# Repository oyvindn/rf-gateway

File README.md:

# rf-gateway

## Hardware

* [ESP32-WROOM-32D](https://www.espressif.com/sites/default/files/documentation/esp32-wroom-32d_esp32-wroom-32u_datasheet_en.pdf)
* [HopeRF RFM69CW 13DBM 868Mhz RF Transceiver Module](https://www.hoperf.com/modules/rf_transceiver/RFM69C.html)
* DS18B20 Digital temperature sensor

## Arduino sketch dependencies

* [Arduino core for the ESP32](https://github.com/espressif/arduino-esp32)
* [Arduino Client for MQTT](https://pubsubclient.knolleary.net/index.html)
* [RadioHead Packet Radio library for embedded microprocessors](http://www.airspayce.com/mikem/arduino/RadioHead/)

## Compile, upload and monitor ESP32 using the Arduino CLI

### Add secrets
Copy `arduino_secrets.h.example` to `arduino_secrets.h` and change the example secret values.

### Download and install Arduino IDE and/or CLI
[Arduino CLI](https://arduino.github.io/arduino-cli/) is an all-in-one solution that provides Boards/Library Managers, sketch builder, board detection, uploader, and many other tools needed to use any Arduino compatible board and platform from command line or machine interfaces.

### Initialiazies a Arduino CLI new configuration:
`arduino-cli config init`

### Add URL for Arduino core for the ESP32, ESP32-S2 and ESP32-C3
Edit `~/Library/Arduino15/arduino-cli.yaml` and add:

```
board_manager:
  additional_urls:
  - https://raw.githubusercontent.com/espressif/arduino-esp32/gh-pages/package_esp32_index.json
```

### Update the core list
`arduino-cli core update-index`

### Install Arduino core for the ESP32, ESP32-S2 and ESP32-C3
`arduino-cli core install esp32:esp32`

### Compile sketch
`arduino-cli compile -b esp32:esp32:esp32 rf-gateway.ino`

### Upload sketch to ESP32:
`arduino-cli upload -p /dev/cu.usbserial-A600K4HV -b esp32:esp32:esp32 rf-gateway.ino`

### Open the serial monitor
`arduino-cli monitor -p /dev/cu.usbserial-A600K4HV -c baudrate=115200`

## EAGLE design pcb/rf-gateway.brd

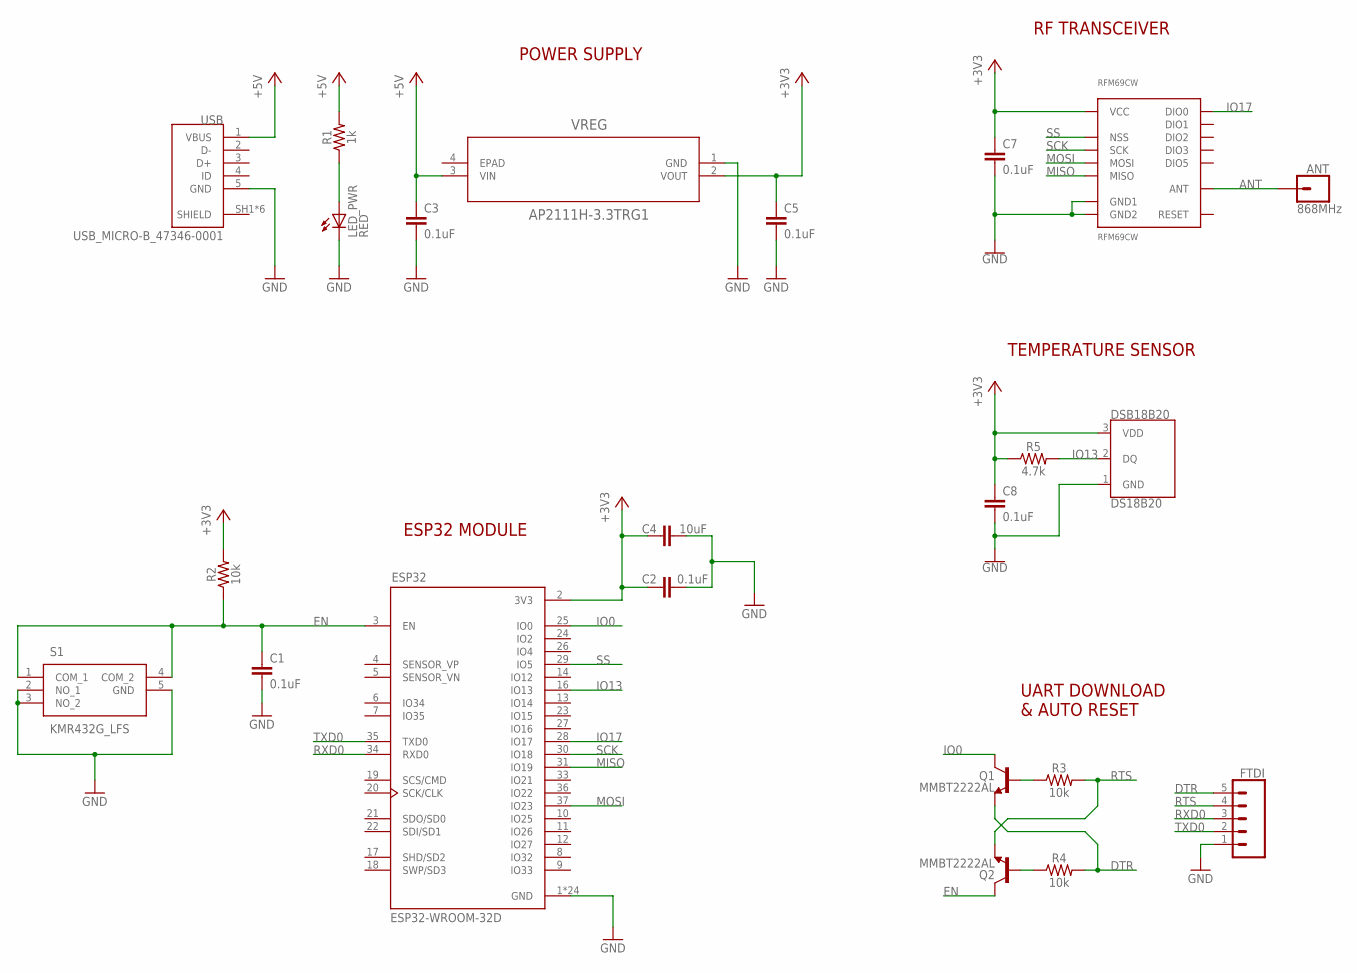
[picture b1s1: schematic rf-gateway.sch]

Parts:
ANT: 868MHz; 1X01
C1, C2, C3, C5, C7, C8: 0.1uF; 0603
C4: 10uF; 0805
DSB18B20: DS18B20; TO-92-AMMO
ESP32: ESP32-WROOM-32D
FTDI: CONN_05; 1X05
LED_PWR: RED; CHIPLED_0805
Q1, Q2: MMBT2222AL; SOT23-3
R1: 1k; 0603
R2, R3, R4: 10k; 0603
R5: 4.7k; 0603
RFM69CW: RFM69CW
S1: KMR432G_LFS; KMR421GULCLFS
USB: USB_MICRO-B_47346-0001; MOLEX_47346-0001
VREG: AP2111H-3.3TRG1; SOT-223_DIO

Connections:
+3V3: C2.1, C4.1, C5.1, C7.1, C8.1, DSB18B20.3 (VDD), ESP32.2 (3V3), R2.2, R5.1, RFM69CW.VDD (VCC), VREG.2 (VOUT)
+5V: C3.1, R1.2, USB.1 (VBUS), VREG.3 (VIN)
ANT: ANT.1, RFM69CW.ANT
DTR: FTDI.5, Q1.2 (E), R4.2
EN: C1.1, ESP32.3 (EN), Q2.3 (C), R2.1, S1.1 (COM_1), S1.4 (COM_2)
GND: C1.2, C2.2, C3.2, C4.2, C5.2, C7.2, C8.2, DSB18B20.1 (GND), ESP32.1 (GND), ESP32.15 (GND), ESP32.38 (GND), ESP32.39_1 (GND), ESP32.39_2 (GND), ESP32.39_3 (GND), ESP32.39_4 (GND), ESP32.39_5 (GND), ESP32.39_6 (GND), ESP32.39_7 (GND), ESP32.39_8 (GND), ESP32.39_9 (GND), ESP32.39_10 (GND), ESP32.39_11 (GND), ESP32.39_12 (GND), ESP32.39_13 (GND), ESP32.39_14 (GND), ESP32.39_15 (GND), ESP32.39_16 (GND), ESP32.39_17 (GND), ESP32.39_18 (GND), ESP32.39_19 (GND), ESP32.39_20 (GND), ESP32.39_21 (GND), FTDI.1, LED_PWR.C, RFM69CW.GND@1 (GND1), RFM69CW.GND@2 (GND2), S1.2 (NO_1), S1.3 (NO_2), S1.5 (GND), USB.5 (GND), VREG.1 (GND)
IO0: ESP32.25 (IO0), Q1.3 (C)
IO13: DSB18B20.2 (DQ), ESP32.16 (IO13), R5.2
IO17: ESP32.28 (IO17), RFM69CW.DIO0
MISO: ESP32.31 (IO19), RFM69CW.MISO
MOSI: ESP32.37 (IO23), RFM69CW.MOSI
unnamed: LED_PWR.A, R1.1
unnamed: Q1.1 (B), R3.1
unnamed: Q2.1 (B), R4.1
RTS: FTDI.4, Q2.2 (E), R3.2
RXD0: ESP32.34 (RXD0), FTDI.3
SCK: ESP32.30 (IO18), RFM69CW.SCK
SS: ESP32.29 (IO5), RFM69CW.NSS
TXD0: ESP32.35 (TXD0), FTDI.2

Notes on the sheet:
ESP32 MODULE
UART DOWNLOAD & AUTO RESET
POWER SUPPLY
RF TRANSCEIVER
TEMPERATURE SENSOR

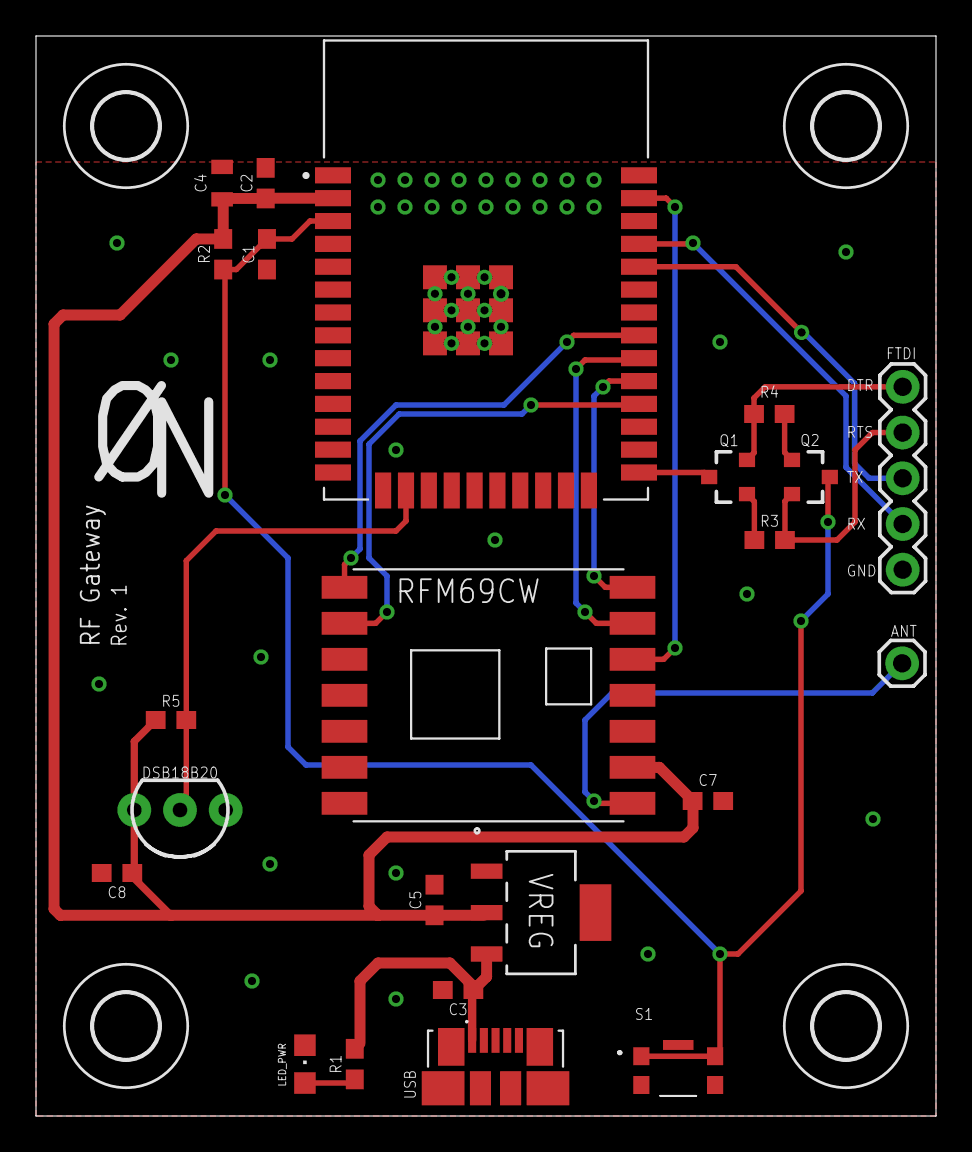
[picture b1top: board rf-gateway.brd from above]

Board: 2 copper layers, 50.0 x 60.0 mm, 27 parts (0 on the bottom side), 19 nets.

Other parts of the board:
U$1, U$2, U$3, U$4: 3,6

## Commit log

2022-03-16 Add more documentation
2022-03-17 Change port to match the ESP32-DevKitC
2022-03-23 Improve MQTT reconnect and add OTA to loop
2022-03-23 Log outgoing MQTT messages
2022-03-23 Println
2022-03-26 Changed from DevKitC to Adafruit HUZZAH32 - ESP32 Feather
2022-06-28 Use the 868 MHz ISM band
2022-06-28 Print actual radio frequency
2022-11-25 Add PCB design rev. 1
2023-01-04 Switch to homemade PCB design
2023-01-17 Add temperature reading inside the enclosure

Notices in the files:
parts and their libraries:
SparkFun-Connectors: Licensing: Creative Commons ShareAlike 4.0 International - https://creativecommons.org/licenses/by-sa/4.0
